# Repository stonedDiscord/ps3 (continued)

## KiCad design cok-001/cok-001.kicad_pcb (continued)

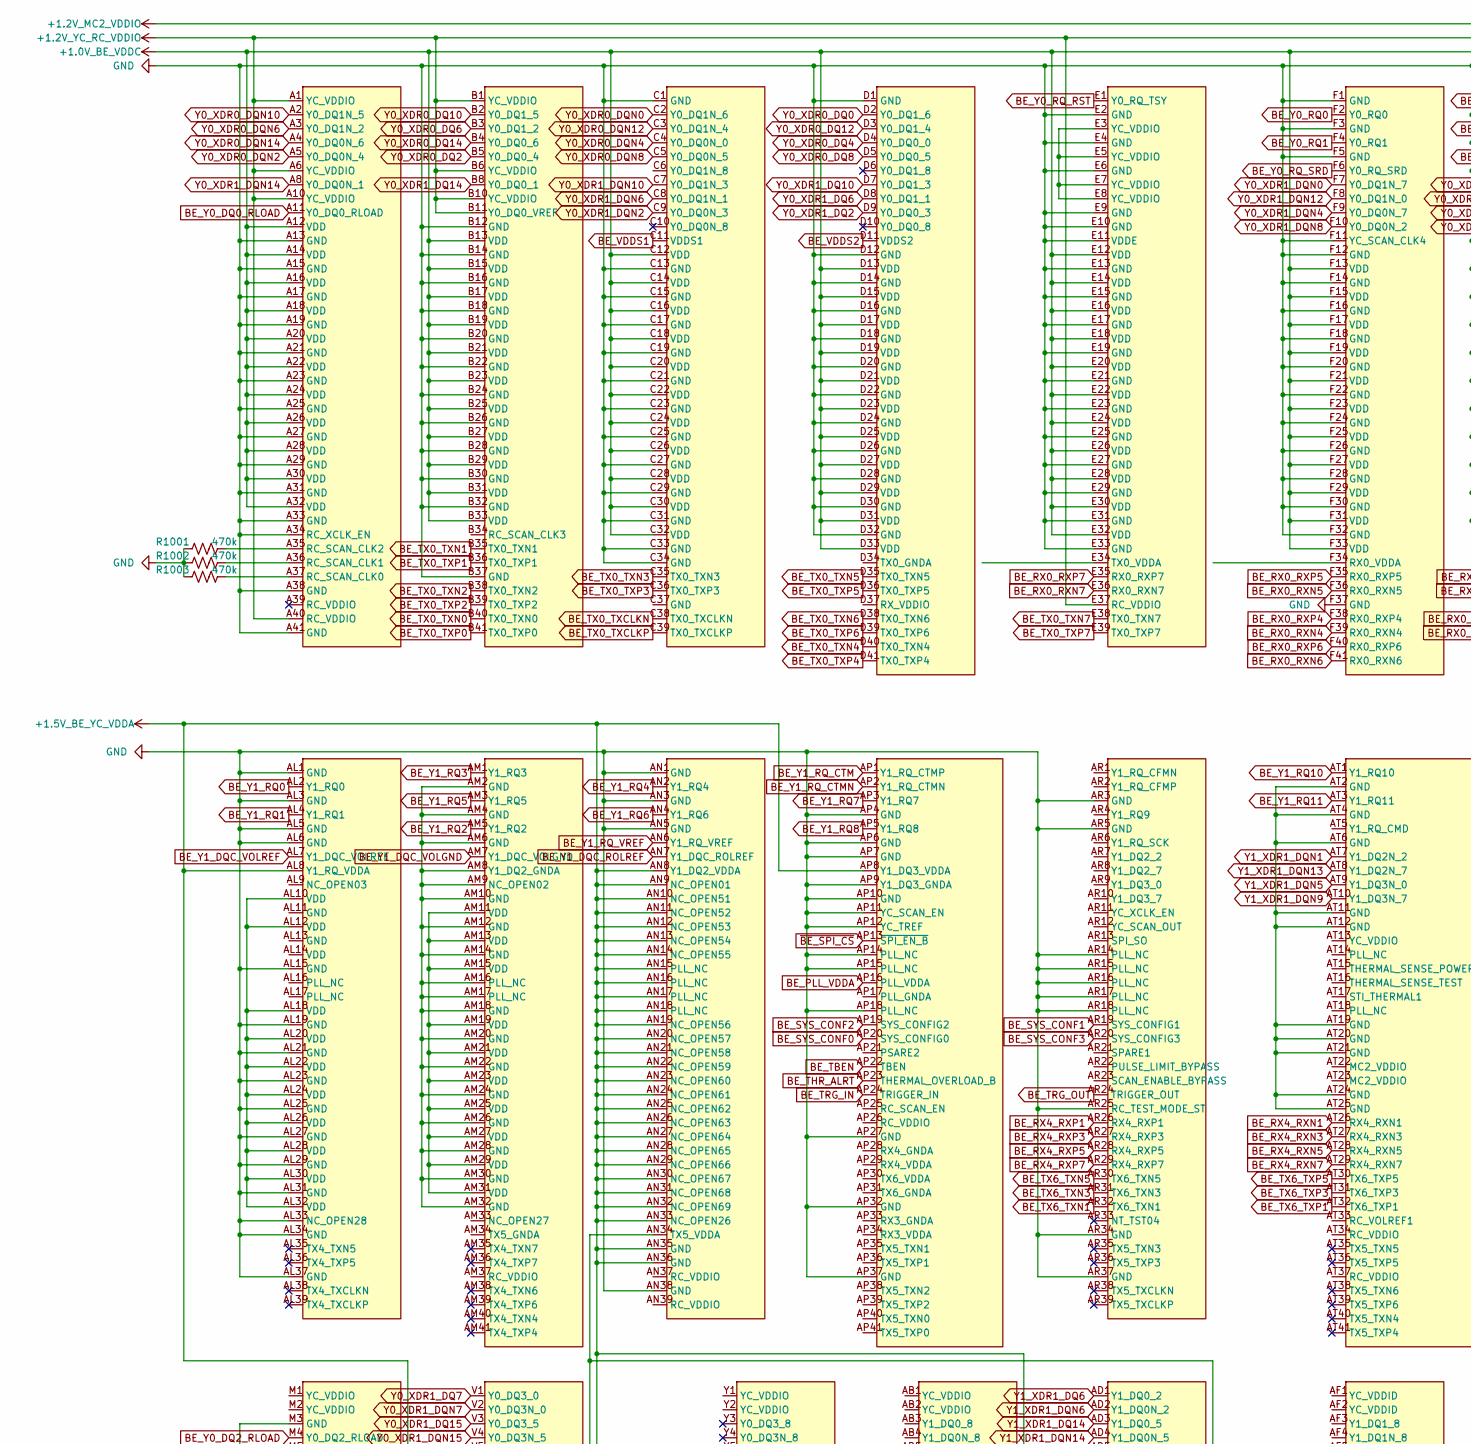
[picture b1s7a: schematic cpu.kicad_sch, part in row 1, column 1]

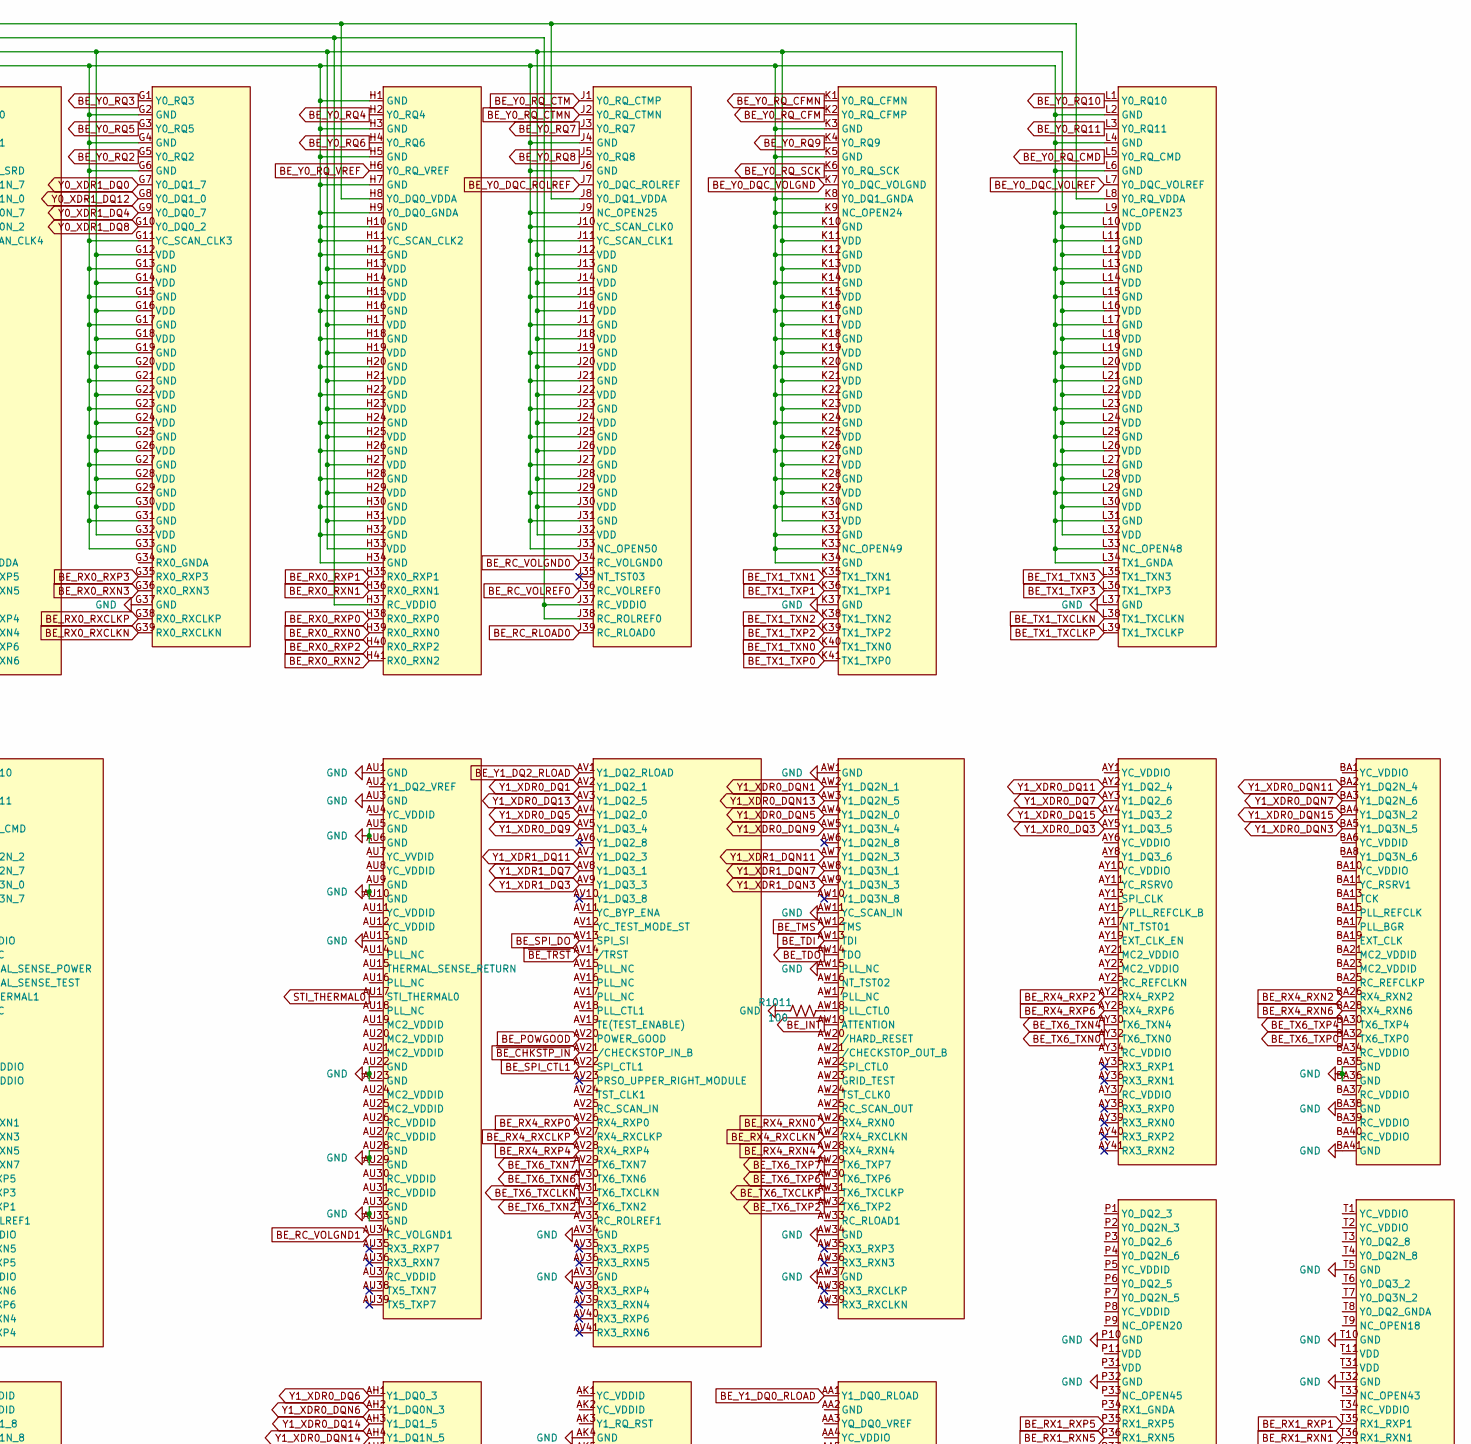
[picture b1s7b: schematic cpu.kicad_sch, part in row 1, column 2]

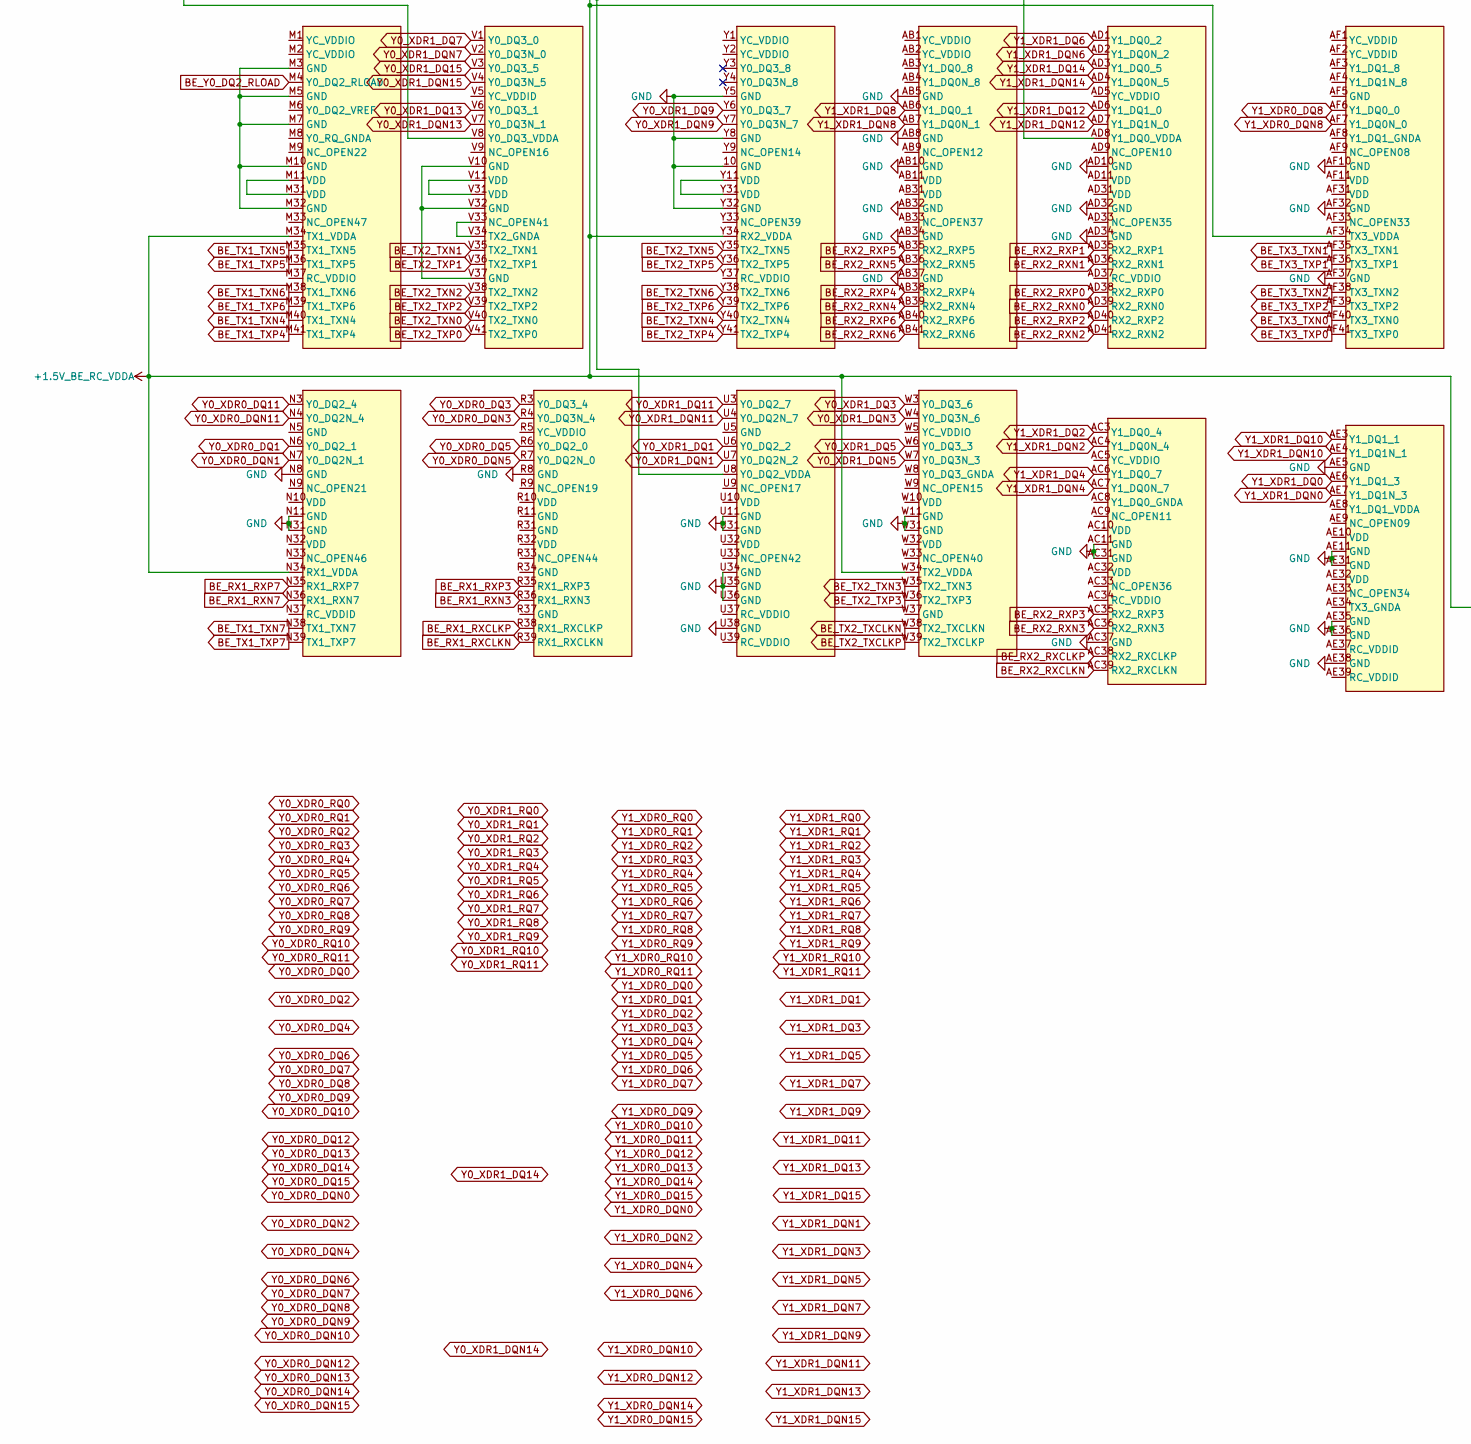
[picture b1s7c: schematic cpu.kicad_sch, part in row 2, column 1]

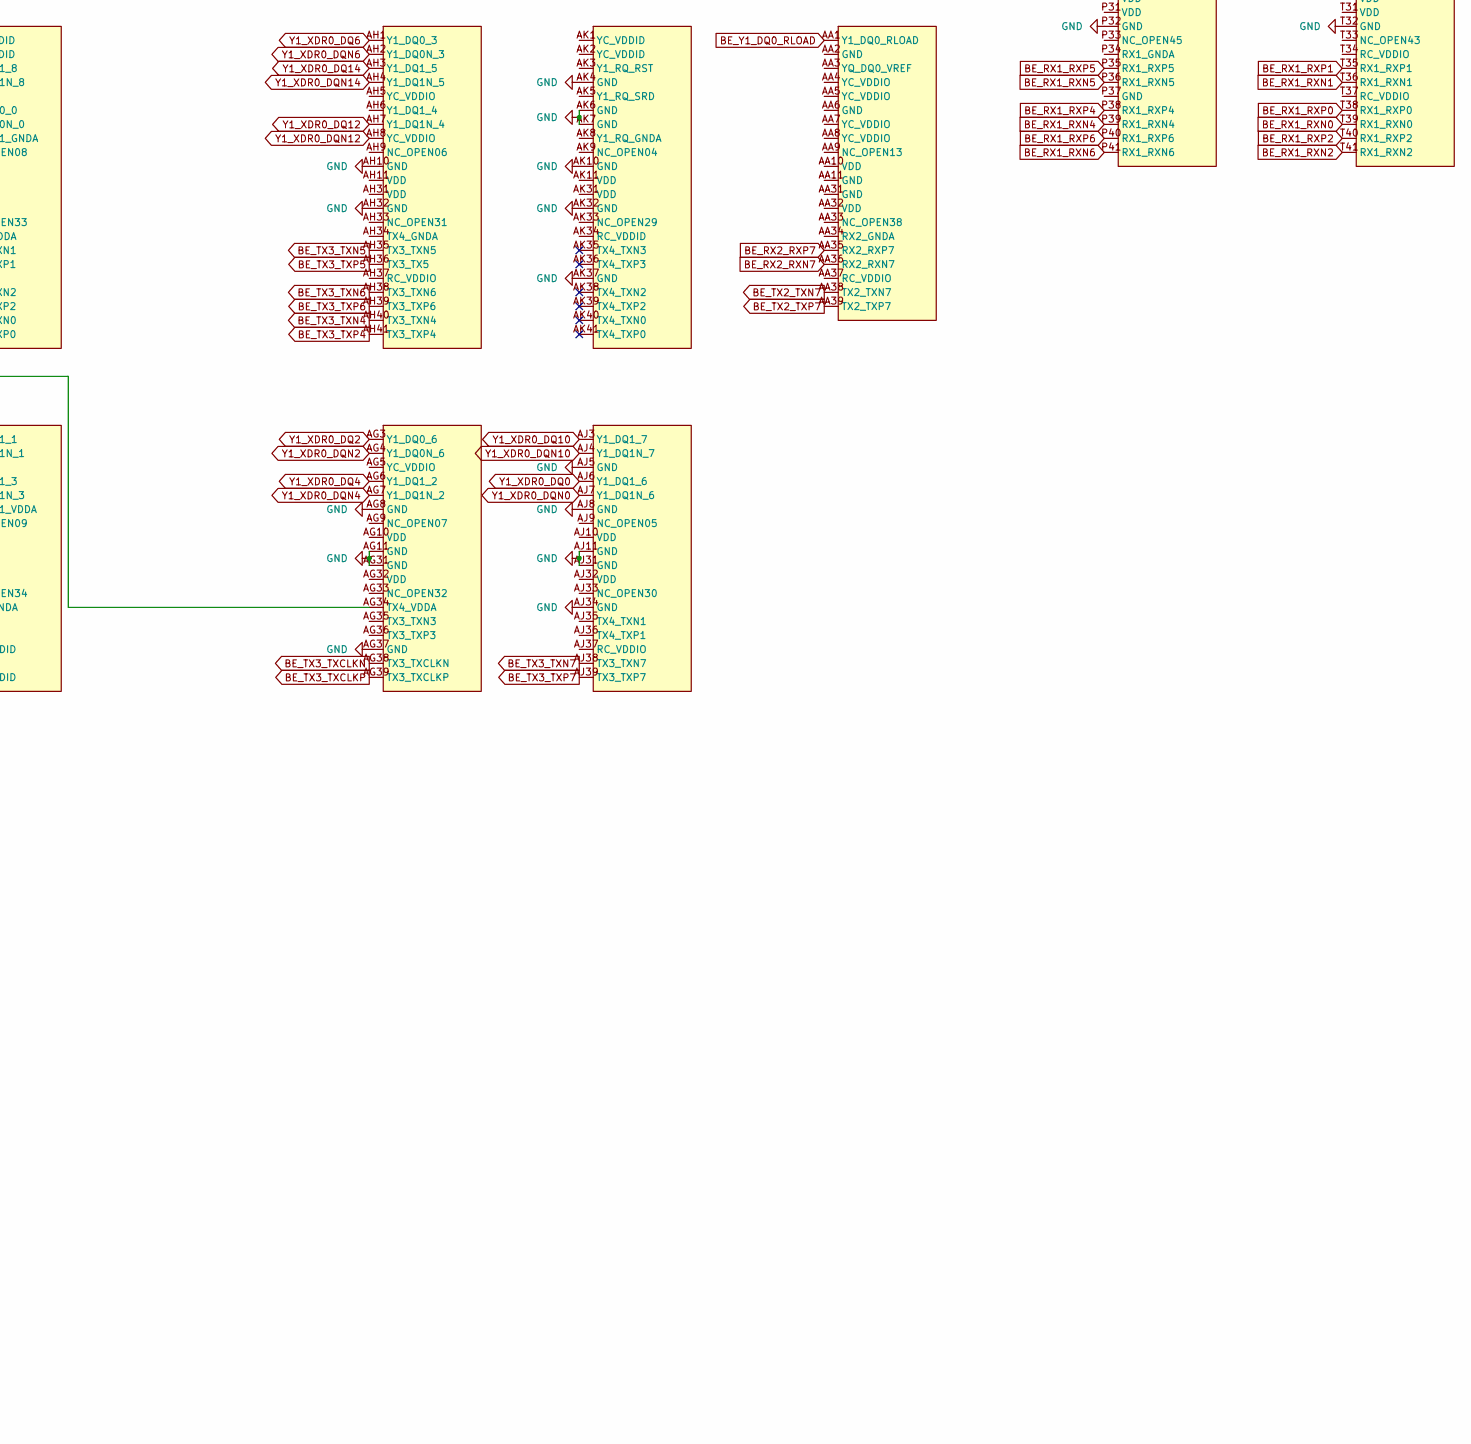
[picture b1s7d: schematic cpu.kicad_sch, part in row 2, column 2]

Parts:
R1001, R1002, R1003: 470k; R_0402_1005Metric
R1011: 100; R_0402_1005Metric
U1001: CELL_multi

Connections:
+1.0V_BE_VDDC: U1001.A12 (VDD), U1001.A14 (VDD), U1001.A16 (VDD), U1001.A18 (VDD), U1001.A20 (VDD), U1001.A22 (VDD), U1001.A24 (VDD), U1001.A26 (VDD), U1001.A28 (VDD), U1001.A30 (VDD), U1001.A32 (VDD), U1001.B13 (VDD), U1001.B15 (VDD), U1001.B17 (VDD), U1001.B19 (VDD), U1001.B21 (VDD), U1001.B23 (VDD), U1001.B25 (VDD), U1001.B27 (VDD), U1001.B29 (VDD), U1001.B31 (VDD), U1001.B33 (VDD), U1001.C12 (VDD), U1001.C14 (VDD), U1001.C16 (VDD), U1001.C18 (VDD), U1001.C20 (VDD), U1001.C22 (VDD), U1001.C24 (VDD), U1001.C26 (VDD), U1001.C28 (VDD), U1001.C30 (VDD), U1001.C32 (VDD), U1001.D13 (VDD), U1001.D15 (VDD), U1001.D17 (VDD), U1001.D19 (VDD), U1001.D21 (VDD), U1001.D23 (VDD), U1001.D25 (VDD), U1001.D27 (VDD), U1001.D29 (VDD), U1001.D31 (VDD), U1001.D33 (VDD), U1001.E12 (VDD), U1001.E14 (VDD), U1001.E16 (VDD), U1001.E18 (VDD), U1001.E20 (VDD), U1001.E22 (VDD), U1001.E24 (VDD), U1001.E26 (VDD), U1001.E28 (VDD), U1001.E30 (VDD), U1001.E32 (VDD), U1001.F13 (VDD), U1001.F15 (VDD), U1001.F17 (VDD), U1001.F19 (VDD), U1001.F21 (VDD), U1001.F23 (VDD), U1001.F25 (VDD), U1001.F27 (VDD), U1001.F29 (VDD), U1001.F31 (VDD), U1001.F33 (VDD), U1001.G12 (VDD), U1001.G14 (VDD), U1001.G16 (VDD), U1001.G18 (VDD), U1001.G20 (VDD), U1001.G22 (VDD), U1001.G24 (VDD), U1001.G26 (VDD), U1001.G28 (VDD), U1001.G30 (VDD), U1001.G32 (VDD), U1001.H13 (VDD), U1001.H15 (VDD), U1001.H17 (VDD), U1001.H19 (VDD), U1001.H21 (VDD), U1001.H23 (VDD), U1001.H25 (VDD), U1001.H27 (VDD), U1001.H29 (VDD), U1001.H31 (VDD), U1001.H33 (VDD), U1001.J12 (VDD), U1001.J14 (VDD), U1001.J16 (VDD), U1001.J18 (VDD), U1001.J20 (VDD), U1001.J22 (VDD), U1001.J24 (VDD), U1001.J26 (VDD), U1001.J28 (VDD), U1001.J30 (VDD), U1001.J32 (VDD), U1001.K11 (VDD), U1001.K13 (VDD), U1001.K15 (VDD), U1001.K17 (VDD), U1001.K19 (VDD), U1001.K21 (VDD), U1001.K23 (VDD), U1001.K25 (VDD), U1001.K27 (VDD), U1001.K29 (VDD), U1001.K31 (VDD), U1001.L10 (VDD), U1001.L12 (VDD), U1001.L14 (VDD), U1001.L16 (VDD), U1001.L18 (VDD), U1001.L20 (VDD), U1001.L22 (VDD), U1001.L24 (VDD), U1001.L26 (VDD), U1001.L28 (VDD), U1001.L30 (VDD), U1001.L32 (VDD); also elsewhere on the board
+1.2V_MC2_VDDIO: U1001.H8 (Y0_DQ0_VDDA), U1001.J8 (Y0_DQ1_VDDA), U1001.L8 (Y0_RQ_VDDA); also elsewhere on the board
+1.2V_YC_RC_VDDIO: U1001.A1 (YC_VDDIO), U1001.A6 (YC_VDDIO), U1001.A10 (YC_VDDIO), U1001.A40 (RC_VDDIO), U1001.B1 (YC_VDDIO), U1001.B6 (YC_VDDIO), U1001.B10 (YC_VDDIO), U1001.B11 (Y0_DQ0_VREF), U1001.E37 (RC_VDDIO), U1001.H37 (RC_VDDIO), U1001.J37 (RC_VDDIO), U1001.J38 (RC_ROLREF0); also elsewhere on the board
+1.5V_BE_RC_VDDA: U1001.AF34 (TX3_VDDA), U1001.AG34 (TX4_VDDA), U1001.AN34 (TX5_VDDA), U1001.M34 (TX1_VDDA), U1001.N34 (RX1_VDDA), U1001.W34 (TX2_VDDA), U1001.Y34 (RX2_VDDA)
+1.5V_BE_YC_VDDA: U1001.AD8 (Y1_DQ0_VDDA), U1001.AL8 (Y1_RQ_VDDA), U1001.AN8 (Y1_DQ2_VDDA), U1001.AN9 (NC_OPEN01), U1001.AN10 (NC_OPEN51), U1001.AN11 (NC_OPEN52), U1001.AN12 (NC_OPEN53), U1001.AN13 (NC_OPEN54), U1001.AN14 (NC_OPEN55), U1001.AN15 (PLL_NC), U1001.AN16 (PLL_NC), U1001.AN17 (PLL_NC), U1001.AN18 (PLL_NC), U1001.AN19 (NC_OPEN56), U1001.AN20 (NC_OPEN57), U1001.AN21 (NC_OPEN58), U1001.AN22 (NC_OPEN59), U1001.AN23 (NC_OPEN60), U1001.AN24 (NC_OPEN61), U1001.AN25 (NC_OPEN62), U1001.AN26 (NC_OPEN63), U1001.AN27 (NC_OPEN64), U1001.AN28 (NC_OPEN65), U1001.AN29 (NC_OPEN66), U1001.AN30 (NC_OPEN67), U1001.AN31 (NC_OPEN68), U1001.AN32 (NC_OPEN69), U1001.AN33 (NC_OPEN26), U1001.AN35 (GND), U1001.AN36 (GND), U1001.AP8 (Y1_DQ3_VDDA), U1001.U8 (Y0_DQ2_VDDA), U1001.V8 (Y0_DQ3_VDDA)
BE_INT: U1001.AW19 (ATTENTION)
BE_PLL_VDDA: U1001.AP16 (PLL_VDDA); also elsewhere on the board
BE_POWGOOD: U1001.AV20 (POWER_GOOD); also elsewhere on the board
BE_RC_RLOAD0: U1001.J39 (RC_RLOAD0); also elsewhere on the board
BE_RC_VOLGND0: U1001.J34 (RC_VOLGND0); also elsewhere on the board
BE_RC_VOLGND1: U1001.AU34 (RC_VOLGND1); also elsewhere on the board
BE_RC_VOLREF0: U1001.J36 (RC_VOLREF0); also elsewhere on the board
BE_RX0_RXCLKN: U1001.G39 (RX0_RXCLKN); also elsewhere on the board
BE_RX0_RXCLKP: U1001.G38 (RX0_RXCLKP); also elsewhere on the board
BE_RX0_RXN0: U1001.H39 (RX0_RXN0); also elsewhere on the board
BE_RX0_RXN1: U1001.H36 (RX0_RXN1); also elsewhere on the board
BE_RX0_RXN2: U1001.H41 (RX0_RXN2); also elsewhere on the board
BE_RX0_RXN3: U1001.G36 (RXO_RXN3); also elsewhere on the board
BE_RX0_RXN4: U1001.F39 (RX0_RXN4); also elsewhere on the board
BE_RX0_RXN5: U1001.F36 (RX0_RXN5); also elsewhere on the board
BE_RX0_RXN6: U1001.F41 (RX0_RXN6); also elsewhere on the board
BE_RX0_RXN7: U1001.E36 (RX0_RXN7); also elsewhere on the board
BE_RX0_RXP0: U1001.H38 (RX0_RXP0); also elsewhere on the board
BE_RX0_RXP1: U1001.H35 (RX0_RXP1); also elsewhere on the board
BE_RX0_RXP2: U1001.H40 (RX0_RXP2); also elsewhere on the board
BE_RX0_RXP3: U1001.G35 (RX0_RXP3); also elsewhere on the board
BE_RX0_RXP4: U1001.F38 (RX0_RXP4); also elsewhere on the board
BE_RX0_RXP5: U1001.F35 (RX0_RXP5); also elsewhere on the board
BE_RX0_RXP6: U1001.F40 (RX0_RXP6); also elsewhere on the board
BE_RX0_RXP7: U1001.E35 (RX0_RXP7); also elsewhere on the board
BE_RX1_RXCLKN: U1001.R39 (RX1_RXCLKN); also elsewhere on the board
BE_RX1_RXCLKP: U1001.R38 (RX1_RXCLKP); also elsewhere on the board
BE_RX1_RXN0: U1001.T39 (RX1_RXN0); also elsewhere on the board
BE_RX1_RXN1: U1001.T36 (RX1_RXN1); also elsewhere on the board
BE_RX1_RXN2: U1001.T41 (RX1_RXN2); also elsewhere on the board
BE_RX1_RXN3: U1001.R36 (RX1_RXN3); also elsewhere on the board
BE_RX1_RXN4: U1001.P39 (RX1_RXN4); also elsewhere on the board
BE_RX1_RXN5: U1001.P36 (RX1_RXN5); also elsewhere on the board
BE_RX1_RXN6: U1001.P41 (RX1_RXN6); also elsewhere on the board
BE_RX1_RXN7: U1001.N36 (RX1_RXN7); also elsewhere on the board
BE_RX1_RXP0: U1001.T38 (RX1_RXP0); also elsewhere on the board
BE_RX1_RXP1: U1001.T35 (RX1_RXP1); also elsewhere on the board
BE_RX1_RXP2: U1001.T40 (RX1_RXP2); also elsewhere on the board
BE_RX1_RXP3: U1001.R35 (RX1_RXP3); also elsewhere on the board
BE_RX1_RXP4: U1001.P38 (RX1_RXP4); also elsewhere on the board
BE_RX1_RXP5: U1001.P35 (RX1_RXP5); also elsewhere on the board
BE_RX1_RXP6: U1001.P40 (RX1_RXP6); also elsewhere on the board
BE_RX1_RXP7: U1001.N35 (RX1_RXP7); also elsewhere on the board
BE_RX2_RXCLKN: U1001.AC39 (RX2_RXCLKN); also elsewhere on the board
BE_RX2_RXCLKP: U1001.AC38 (RX2_RXCLKP); also elsewhere on the board
BE_RX2_RXN0: U1001.AD39 (RX2_RXN0); also elsewhere on the board
BE_RX2_RXN1: U1001.AD36 (RX2_RXN1)
BE_RX2_RXN2: U1001.AD41 (RX2_RXN2); also elsewhere on the board
BE_RX2_RXN3: U1001.AC36 (RX2_RXN3); also elsewhere on the board
BE_RX2_RXN4: U1001.AB39 (RX2_RXN4); also elsewhere on the board
BE_RX2_RXN5: U1001.AB36 (RX2_RXN5); also elsewhere on the board
BE_RX2_RXN6: U1001.AB41 (RX2_RXN6); also elsewhere on the board
BE_RX2_RXN7: U1001.AA36 (RX2_RXN7); also elsewhere on the board
BE_RX2_RXP0: U1001.AD38 (RX2_RXP0); also elsewhere on the board
BE_RX2_RXP1: U1001.AD35 (RX2_RXP1)
BE_RX2_RXP2: U1001.AD40 (RX2_RXP2); also elsewhere on the board
BE_RX2_RXP3: U1001.AC35 (RX2_RXP3); also elsewhere on the board
BE_RX2_RXP4: U1001.AB38 (RX2_RXP4); also elsewhere on the board
BE_RX2_RXP5: U1001.AB35 (RX2_RXP5); also elsewhere on the board
BE_RX2_RXP6: U1001.AB40 (RX2_RXP6); also elsewhere on the board
BE_RX2_RXP7: U1001.AA35 (RX2_RXP7); also elsewhere on the board
BE_RX4_RXCLKN: U1001.AW27 (RX4_RXCLKN); also elsewhere on the board
BE_RX4_RXCLKP: U1001.AV27 (RX4_RXCLKP); also elsewhere on the board
BE_RX4_RXN0: U1001.AW26 (RX4_RXN0); also elsewhere on the board
BE_RX4_RXN1: U1001.AT26 (RX4_RXN1); also elsewhere on the board
BE_RX4_RXN2: U1001.BA26 (RX4_RXN2); also elsewhere on the board
BE_RX4_RXN3: U1001.AT27 (RX4_RXN3); also elsewhere on the board
BE_RX4_RXN4: U1001.AW28 (RX4_RXN4); also elsewhere on the board
BE_RX4_RXN5: U1001.AT28 (RX4_RXN5); also elsewhere on the board
BE_RX4_RXN6: U1001.BA28 (RX4_RXN6); also elsewhere on the board
BE_RX4_RXN7: U1001.AT29 (RX4_RXN7); also elsewhere on the board
BE_RX4_RXP0: U1001.AV26 (RX4_RXP0); also elsewhere on the board
BE_RX4_RXP1: U1001.AR26 (RX4_RXP1); also elsewhere on the board
BE_RX4_RXP2: U1001.AY26 (RX4_RXP2); also elsewhere on the board
BE_RX4_RXP3: U1001.AR27 (RX4_RXP3); also elsewhere on the board
BE_RX4_RXP4: U1001.AV28 (RX4_RXP4); also elsewhere on the board
BE_RX4_RXP5: U1001.AR28 (RX4_RXP5); also elsewhere on the board
BE_RX4_RXP6: U1001.AY28 (RX4_RXP6); also elsewhere on the board
BE_RX4_RXP7: U1001.AR29 (RX4_RXP7); also elsewhere on the board
BE_SPI_CTL1: U1001.AV22 (SPI_CTL1); also elsewhere on the board
BE_SPI_DO: U1001.AV13 (SPI_SI); also elsewhere on the board
BE_SYS_CONF0: U1001.AP20 (SYS_CONFIG0); also elsewhere on the board
BE_SYS_CONF1: U1001.AR19 (SYS_CONFIG1); also elsewhere on the board
BE_SYS_CONF2: U1001.AP19 (SYS_CONFIG2); also elsewhere on the board
BE_SYS_CONF3: U1001.AR20 (SYS_CONFIG3); also elsewhere on the board
BE_TBEN: U1001.AP22 (TBEN); also elsewhere on the board
BE_TDI: U1001.AW13 (TDI); also elsewhere on the board
BE_TDO: U1001.AW14 (TDO); also elsewhere on the board
BE_THR_ALRT: U1001.AP23 (THERMAL_OVERLOAD_B); also elsewhere on the board
BE_TMS: U1001.AW12 (TMS); also elsewhere on the board
BE_TRG_IN: U1001.AP24 (TRIGGER_IN); also elsewhere on the board
BE_TRG_OUT: U1001.AR24 (TRIGGER_OUT); also elsewhere on the board
BE_TX0_TXCLKN: U1001.C38 (TX0_TXCLKN); also elsewhere on the board
BE_TX0_TXCLKP: U1001.C39 (TX0_TXCLKP); also elsewhere on the board
BE_TX0_TXN0: U1001.B40 (TX0_TXN0); also elsewhere on the board
BE_TX0_TXN1: U1001.B35 (TX0_TXN1); also elsewhere on the board
BE_TX0_TXN2: U1001.B38 (TX0_TXN2); also elsewhere on the board
BE_TX0_TXN3: U1001.C35 (TX0_TXN3); also elsewhere on the board
BE_TX0_TXN4: U1001.D40 (TX0_TXN4); also elsewhere on the board
BE_TX0_TXN5: U1001.D35 (TX0_TXN5); also elsewhere on the board
BE_TX0_TXN6: U1001.D38 (TX0_TXN6); also elsewhere on the board
BE_TX0_TXN7: U1001.E38 (TX0_TXN7); also elsewhere on the board
BE_TX0_TXP0: U1001.B41 (TX0_TXP0); also elsewhere on the board
BE_TX0_TXP1: U1001.B36 (TX0_TXP1); also elsewhere on the board
BE_TX0_TXP2: U1001.B39 (TX0_TXP2); also elsewhere on the board
BE_TX0_TXP3: U1001.C36 (TX0_TXP3); also elsewhere on the board
BE_TX0_TXP4: U1001.D41 (TX0_TXP4); also elsewhere on the board
BE_TX0_TXP5: U1001.D36 (TX0_TXP5); also elsewhere on the board
BE_TX0_TXP6: U1001.D39 (TX0_TXP6); also elsewhere on the board
BE_TX0_TXP7: U1001.E39 (TX0_TXP7); also elsewhere on the board
BE_TX1_TXCLKN: U1001.L38 (TX1_TXCLKN); also elsewhere on the board
BE_TX1_TXCLKP: U1001.L39 (TX1_TXCLKP); also elsewhere on the board
BE_TX1_TXN0: U1001.K40 (TX1_TXN0); also elsewhere on the board
BE_TX1_TXN1: U1001.K35 (TX1_TXN1); also elsewhere on the board
BE_TX1_TXN2: U1001.K38 (TX1_TXN2); also elsewhere on the board
BE_TX1_TXN3: U1001.L35 (TX1_TXN3); also elsewhere on the board
BE_TX1_TXN4: U1001.M40 (TX1_TXN4); also elsewhere on the board
BE_TX1_TXN5: U1001.M35 (TX1_TXN5); also elsewhere on the board
BE_TX1_TXN6: U1001.M38 (TX1_TXN6); also elsewhere on the board
BE_TX1_TXN7: U1001.N38 (TX1_TXN7); also elsewhere on the board
BE_TX1_TXP0: U1001.K41 (TX1_TXP0); also elsewhere on the board
BE_TX1_TXP1: U1001.K36 (TX1_TXP1); also elsewhere on the board
BE_TX1_TXP2: U1001.K39 (TX1_TXP2); also elsewhere on the board
BE_TX1_TXP3: U1001.L36 (TX1_TXP3); also elsewhere on the board
BE_TX1_TXP4: U1001.M41 (TX1_TXP4); also elsewhere on the board
BE_TX1_TXP5: U1001.M36 (TX1_TXP5); also elsewhere on the board
BE_TX1_TXP6: U1001.M39 (TX1_TXP6); also elsewhere on the board
BE_TX1_TXP7: U1001.N39 (TX1_TXP7); also elsewhere on the board
BE_TX2_TXCLKN: U1001.W38 (TX2_TXCLKN); also elsewhere on the board
BE_TX2_TXCLKP: U1001.W39 (TX2_TXCLKP); also elsewhere on the board
BE_TX2_TXN0: U1001.V40 (TX2_TXN0); also elsewhere on the board
BE_TX2_TXN1: U1001.V35 (TX2_TXN1); also elsewhere on the board
BE_TX2_TXN2: U1001.V38 (TX2_TXN2); also elsewhere on the board
BE_TX2_TXN3: U1001.W35 (TX2_TXN3); also elsewhere on the board
BE_TX2_TXN4: U1001.Y40 (TX2_TXN4); also elsewhere on the board
BE_TX2_TXN5: U1001.Y35 (TX2_TXN5); also elsewhere on the board
BE_TX2_TXN6: U1001.Y38 (TX2_TXN6); also elsewhere on the board
BE_TX2_TXN7: U1001.AA38 (TX2_TXN7); also elsewhere on the board
BE_TX2_TXP0: U1001.V41 (TX2_TXP0); also elsewhere on the board
BE_TX2_TXP1: U1001.V36 (TX2_TXP1); also elsewhere on the board
BE_TX2_TXP2: U1001.V39 (TX2_TXP2); also elsewhere on the board
BE_TX2_TXP3: U1001.W36 (TX2_TXP3); also elsewhere on the board
BE_TX2_TXP4: U1001.Y41 (TX2_TXP4); also elsewhere on the board
BE_TX2_TXP5: U1001.Y36 (TX2_TXP5); also elsewhere on the board
BE_TX2_TXP6: U1001.Y39 (TX2_TXP6); also elsewhere on the board
BE_TX2_TXP7: U1001.AA39 (TX2_TXP7); also elsewhere on the board
BE_TX3_TXCLKN: U1001.AG38 (TX3_TXCLKN); also elsewhere on the board
BE_TX3_TXCLKP: U1001.AG39 (TX3_TXCLKP); also elsewhere on the board
BE_TX3_TXN0: U1001.AF40 (TX3_TXN0); also elsewhere on the board
BE_TX3_TXN1: U1001.AF35 (TX3_TXN1); also elsewhere on the board
BE_TX3_TXN2: U1001.AF38 (TX3_TXN2); also elsewhere on the board
BE_TX3_TXN4: U1001.AH40 (TX3_TXN4); also elsewhere on the board
BE_TX3_TXN5: U1001.AH35 (TX3_TXN5); also elsewhere on the board
BE_TX3_TXN6: U1001.AH38 (TX3_TXN6); also elsewhere on the board
BE_TX3_TXN7: U1001.AJ38 (TX3_TXN7); also elsewhere on the board
BE_TX3_TXP0: U1001.AF41 (TX3_TXP0); also elsewhere on the board
BE_TX3_TXP1: U1001.AF36 (TX3_TXP1); also elsewhere on the board
BE_TX3_TXP2: U1001.AF39 (TX3_TXP2); also elsewhere on the board
BE_TX3_TXP4: U1001.AH41 (TX3_TXP4); also elsewhere on the board
BE_TX3_TXP5: U1001.AH36 (TX3_TX5); also elsewhere on the board
BE_TX3_TXP6: U1001.AH39 (TX3_TXP6); also elsewhere on the board
BE_TX3_TXP7: U1001.AJ39 (TX3_TXP7); also elsewhere on the board
BE_TX6_TXCLKN: U1001.AV31 (TX6_TXCLKN); also elsewhere on the board
BE_TX6_TXCLKP: U1001.AW31 (TX6_TXCLKP); also elsewhere on the board
BE_TX6_TXN0: U1001.AY32 (TX6_TXN0); also elsewhere on the board
BE_TX6_TXN1: U1001.AR32 (TX6_TXN1); also elsewhere on the board
BE_TX6_TXN2: U1001.AV32 (TX6_TXN2); also elsewhere on the board
BE_TX6_TXN3: U1001.AR31 (TX6_TXN3); also elsewhere on the board
BE_TX6_TXN4: U1001.AY30 (TX6_TXN4); also elsewhere on the board
BE_TX6_TXN5: U1001.AR30 (TX6_TXN5); also elsewhere on the board
BE_TX6_TXN6: U1001.AV30 (TX6_TXN6); also elsewhere on the board
BE_TX6_TXN7: U1001.AV29 (TX6_TXN7); also elsewhere on the board
BE_TX6_TXP0: U1001.BA32 (TX6_TXP0); also elsewhere on the board
BE_TX6_TXP1: U1001.AT32 (TX6_TXP1); also elsewhere on the board
BE_TX6_TXP2: U1001.AW32 (TX6_TXP2); also elsewhere on the board
BE_TX6_TXP3: U1001.AT31 (TX6_TXP3); also elsewhere on the board
BE_TX6_TXP4: U1001.BA30 (TX6_TXP4); also elsewhere on the board
BE_TX6_TXP5: U1001.AT30 (TX6_TXP5); also elsewhere on the board
BE_TX6_TXP6: U1001.AW30 (TX6_TXP6); also elsewhere on the board
BE_TX6_TXP7: U1001.AW29 (TX6_TXP7); also elsewhere on the board
BE_VDDS1: U1001.C11 (VDDS1)
BE_VDDS2: U1001.D11 (VDDS2); also elsewhere on the board
BE_Y0_DQ0_RLOAD: U1001.A11 (Y0_DQ0_RLOAD); also elsewhere on the board
BE_Y0_DQ2_RLOAD: U1001.M4 (Y0_DQ2_RLOAD); also elsewhere on the board
BE_Y0_DQC_ROLREF: U1001.J7 (Y0_DQC_ROLREF); also elsewhere on the board
BE_Y0_DQC_VOLGND: U1001.K7 (Y0_DQC_VOLGND); also elsewhere on the board
BE_Y0_DQC_VOLREF: U1001.L7 (Y0_DQC_VOLREF); also elsewhere on the board
BE_Y0_RQ0: U1001.F2 (Y0_RQ0); also elsewhere on the board
BE_Y0_RQ1: U1001.F4 (Y0_RQ1); also elsewhere on the board
BE_Y0_RQ2: U1001.G5 (Y0_RQ2); also elsewhere on the board
BE_Y0_RQ3: U1001.G1 (Y0_RQ3); also elsewhere on the board
BE_Y0_RQ4: U1001.H2 (Y0_RQ4); also elsewhere on the board
BE_Y0_RQ5: U1001.G3 (Y0_RQ5); also elsewhere on the board
BE_Y0_RQ6: U1001.H4 (Y0_RQ6); also elsewhere on the board
BE_Y0_RQ7: U1001.J3 (Y0_RQ7); also elsewhere on the board
BE_Y0_RQ8: U1001.J5 (Y0_RQ8); also elsewhere on the board
BE_Y0_RQ9: U1001.K4 (Y0_RQ9); also elsewhere on the board
BE_Y0_RQ10: U1001.L1 (Y0_RQ10); also elsewhere on the board
BE_Y0_RQ11: U1001.L3 (Y0_RQ11); also elsewhere on the board
BE_Y0_RQ_CFM: U1001.K2 (Y0_RQ_CFMP); also elsewhere on the board
BE_Y0_RQ_CFMN: U1001.K1 (Y0_RQ_CFMN); also elsewhere on the board
BE_Y0_RQ_CMD: U1001.L5 (Y0_RQ_CMD)
BE_Y0_RQ_CTM: U1001.J1 (Y0_RQ_CTMP)
BE_Y0_RQ_CTMN: U1001.J2 (Y0_RQ_CTMN)
BE_Y0_RQ_RST: U1001.E1 (Y0_RQ_TSY)
BE_Y0_RQ_SCK: U1001.K6 (Y0_RQ_SCK); also elsewhere on the board
BE_Y0_RQ_SRD: U1001.F6 (Y0_RQ_SRD)
BE_Y0_RQ_VREF: U1001.H6 (Y0_RQ_VREF)
BE_Y1_DQ0_RLOAD: U1001.AA1 (Y1_DQ0_RLOAD); also elsewhere on the board
BE_Y1_DQ2_RLOAD: U1001.AV1 (Y1_DQ2_RLOAD); also elsewhere on the board
BE_Y1_DQC_ROLREF: U1001.AN7 (Y1_DQC_ROLREF); also elsewhere on the board
BE_Y1_DQC_VOLGND: U1001.AM7 (Y1_DQC_VOLGND); also elsewhere on the board
BE_Y1_DQC_VOLREF: U1001.AL7 (Y1_DQC_VOLREF); also elsewhere on the board
BE_Y1_RQ0: U1001.AL2 (Y1_RQ0); also elsewhere on the board
BE_Y1_RQ1: U1001.AL4 (Y1_RQ1); also elsewhere on the board
BE_Y1_RQ2: U1001.AM5 (Y1_RQ2); also elsewhere on the board
BE_Y1_RQ3: U1001.AM1 (Y1_RQ3); also elsewhere on the board
BE_Y1_RQ4: U1001.AN2 (Y1_RQ4); also elsewhere on the board
BE_Y1_RQ5: U1001.AM3 (Y1_RQ5); also elsewhere on the board
BE_Y1_RQ6: U1001.AN4 (Y1_RQ6); also elsewhere on the board
BE_Y1_RQ7: U1001.AP3 (Y1_RQ7); also elsewhere on the board
BE_Y1_RQ8: U1001.AP5 (Y1_RQ8); also elsewhere on the board
BE_Y1_RQ10: U1001.AT1 (Y1_RQ10); also elsewhere on the board
BE_Y1_RQ11: U1001.AT3 (Y1_RQ11); also elsewhere on the board
BE_Y1_RQ_CTM: U1001.AP1 (Y1_RQ_CTMP)
BE_Y1_RQ_CTMN: U1001.AP2 (Y1_RQ_CTMN)
BE_Y1_RQ_VREF: U1001.AN6 (Y1_RQ_VREF)
GND: R1001.1, R1002.1, R1003.1, R1011.1, U1001.10 (GND), U1001.A13 (GND), U1001.A15 (GND), U1001.A17 (GND), U1001.A19 (GND), U1001.A21 (GND), U1001.A23 (GND), U1001.A25 (GND), U1001.A27 (GND), U1001.A29 (GND), U1001.A31 (GND), U1001.A33 (GND), U1001.A34 (RC_XCLK_EN), U1001.A38 (GND), U1001.A41 (GND), U1001.AB5 (GND), U1001.AB8 (GND), U1001.AB10 (GND), U1001.AB32 (GND), U1001.AB34 (GND), U1001.AB37 (GND), U1001.AC11 (GND), U1001.AC31 (GND), U1001.AC37 (GND), U1001.AD10 (GND), U1001.AD32 (GND), U1001.AD34 (GND), U1001.AE5 (GND), U1001.AE11 (GND), U1001.AE31 (GND), U1001.AE35 (GND), U1001.AE36 (GND), U1001.AE38 (GND), U1001.AF10 (GND), U1001.AF32 (GND), U1001.AF37 (GND), U1001.AG8 (GND), U1001.AG11 (GND), U1001.AG31 (GND), U1001.AG37 (GND), U1001.AH10 (GND), U1001.AH32 (GND), U1001.AJ5 (GND), U1001.AJ8 (GND), U1001.AJ11 (GND), U1001.AJ31 (GND), U1001.AJ34 (GND), U1001.AK4 (GND), U1001.AK6 (GND), U1001.AK7 (GND), U1001.AK10 (GND), U1001.AK32 (GND), U1001.AK37 (GND), U1001.AL1 (GND), U1001.AL3 (GND), U1001.AL5 (GND), U1001.AL6 (GND), U1001.AL15 (GND), U1001.AL19 (GND), U1001.AL21 (GND), U1001.AL23 (GND), U1001.AL25 (GND), U1001.AL27 (GND), U1001.AL29 (GND), U1001.AL31 (GND), U1001.AL33 (NC_OPEN28), U1001.AL34 (GND), U1001.AL37 (GND), U1001.AN1 (GND), U1001.AN3 (GND), U1001.AN5 (GND), U1001.AN38 (GND), U1001.AP4 (GND), U1001.AP6 (GND), U1001.AP7 (GND), U1001.AP9 (Y1_DQ3_GNDA), U1001.AP10 (GND), U1001.AP11 (YC_SCAN_EN), U1001.AP12 (YC_TREF), U1001.AP14 (PLL_NC), U1001.AP15 (PLL_NC), U1001.AP18 (PLL_NC), U1001.AP27 (GND), U1001.AP32 (GND), U1001.AP37 (GND), U1001.AR3 (GND), U1001.AR5 (GND), U1001.AR14 (PLL_NC), U1001.AR15 (PLL_NC), U1001.AR16 (PLL_NC), U1001.AR17 (PLL_NC), U1001.AR18 (PLL_NC), U1001.AR25 (RC_TEST_MODE_ST), U1001.AR34 (GND), U1001.AR37 (GND), U1001.AU1 (GND), U1001.AU3 (GND), U1001.AU5 (GND), U1001.AU6 (GND), U1001.AU9 (GND), U1001.AU10 (GND), U1001.AU13 (GND), U1001.AU22 (GND), U1001.AU23 (GND), U1001.AU28 (GND), U1001.AU29 (GND), U1001.AU32 (GND), U1001.AU33 (GND), U1001.AV34 (GND), U1001.AV37 (GND), U1001.AW1 (GND), U1001.AW11 (YC_SCAN_IN), U1001.AW15 (PLL_NC), U1001.AW34 (GND), U1001.AW37 (GND), U1001.B12 (GND), U1001.B14 (GND), U1001.B16 (GND), U1001.B18 (GND), U1001.B20 (GND), U1001.B22 (GND), U1001.B24 (GND), U1001.B26 (GND), U1001.B28 (GND), U1001.B30 (GND), U1001.B32 (GND), U1001.B37 (GND), U1001.BA35 (GND), U1001.BA36 (GND), U1001.BA38 (GND), U1001.BA41 (GND), U1001.C1 (GND), U1001.C13 (GND), U1001.C15 (GND), U1001.C17 (GND), U1001.C19 (GND), U1001.C21 (GND), U1001.C23 (GND), U1001.C25 (GND), U1001.C27 (GND), U1001.C29 (GND), U1001.C31 (GND), U1001.C33 (GND), U1001.C34 (GND), U1001.D1 (GND), U1001.D12 (GND), U1001.D14 (GND), U1001.D16 (GND), U1001.D18 (GND), U1001.D20 (GND), U1001.D22 (GND), U1001.D24 (GND), U1001.D26 (GND), U1001.D28 (GND), U1001.D30 (GND), U1001.D32 (GND), U1001.E2 (GND), U1001.E4 (GND), U1001.E6 (GND), U1001.E9 (GND), U1001.E10 (GND), U1001.E11 (VDDE), U1001.E13 (GND), U1001.E15 (GND), U1001.E17 (GND), U1001.E19 (GND), U1001.E21 (GND), U1001.E23 (GND), U1001.E25 (GND), U1001.E27 (GND), U1001.E29 (GND), U1001.E31 (GND), U1001.E33 (GND), U1001.F1 (GND), U1001.F3 (GND), U1001.F5 (GND), U1001.F11 (YC_SCAN_CLK4), U1001.F12 (GND), U1001.F14 (GND), U1001.F16 (GND), U1001.F18 (GND), U1001.F20 (GND), U1001.F22 (GND), U1001.F24 (GND), U1001.F26 (GND), U1001.F28 (GND), U1001.F30 (GND), U1001.F32 (GND), U1001.F37 (GND), U1001.G2 (GND), U1001.G4 (GND), U1001.G6 (GND), U1001.G11 (YC_SCAN_CLK3), U1001.G13 (GND), U1001.G15 (GND), U1001.G17 (GND), U1001.G19 (GND), U1001.G21 (GND), U1001.G23 (GND), U1001.G25 (GND), U1001.G27 (GND), U1001.G29 (GND), U1001.G31 (GND), U1001.G33 (GND), U1001.G37 (GND)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; also elsewhere on the board
unnamed: R1003.2, U1001.A37 (RC_SCAN_CLK0)
unnamed: R1002.2, U1001.A36 (RC_SCAN_CLK1)
unnamed: R1001.2, U1001.A35 (RC_SCAN_CLK2)
unnamed: U1001.AL10 (VDD), U1001.AL12 (VDD), U1001.AL18 (VDD), U1001.AL20 (VDD), U1001.AL22 (VDD), U1001.AL24 (VDD), U1001.AL26 (VDD), U1001.AL28 (VDD), U1001.AL30 (VDD), U1001.AL32 (VDD)
unnamed: U1001.AM2 (GND), U1001.AM4 (GND), U1001.AM6 (GND), U1001.AM8 (Y1_DQ2_GNDA), U1001.AM9 (NC_OPEN02), U1001.AM10 (GND), U1001.AM12 (GND), U1001.AM14 (GND), U1001.AM16 (PLL_NC), U1001.AM17 (PLL_NC), U1001.AM18 (GND), U1001.AM20 (GND), U1001.AM22 (GND), U1001.AM24 (GND), U1001.AM26 (GND), U1001.AM28 (GND), U1001.AM30 (GND), U1001.AM32 (GND)
unnamed: U1001.AM11 (VDD), U1001.AM13 (VDD), U1001.AM15 (VDD), U1001.AM19 (VDD), U1001.AM21 (VDD), U1001.AM23 (VDD), U1001.AM25 (VDD), U1001.AM27 (VDD), U1001.AM29 (VDD), U1001.AM31 (VDD)
unnamed: U1001.AT2 (GND), U1001.AT4 (GND), U1001.AT6 (GND), U1001.AT11 (GND), U1001.AT12 (GND), U1001.AT19 (GND), U1001.AT20 (GND), U1001.AT21 (GND), U1001.AT24 (GND), U1001.AT25 (GND)
unnamed: R1011.2, U1001.AW18 (PLL_CTL0)
unnamed: U1001.E3 (YC_VDDIO), U1001.E5 (YC_VDDIO), U1001.E7 (YC_VDDIO), U1001.E8 (YC_VDDIO)
unnamed: U1001.M3 (GND), U1001.M5 (GND), U1001.M7 (GND), U1001.M10 (GND), U1001.M32 (GND)
unnamed: U1001.M11 (VDD), U1001.M31 (VDD)
unnamed: U1001.V10 (GND), U1001.V32 (GND), U1001.V37 (GND)
unnamed: U1001.V33 (NC_OPEN41), U1001.V34 (TX2_GNDA)
unnamed: U1001.V11 (VDD), U1001.V31 (VDD)
unnamed: U1001.Y11 (VDD), U1001.Y31 (VDD)
STI_THERMAL0: U1001.AU17 (STI_THERMAL0); also elsewhere on the board
Y0_XDR0_DQ0: U1001.D2 (Y0_DQ1_6); also elsewhere on the board
Y0_XDR0_DQ1: U1001.N6 (Y0_DQ2_1); also elsewhere on the board
Y0_XDR0_DQ2: U1001.B5 (Y0_DQ0_4); also elsewhere on the board
Y0_XDR0_DQ3: U1001.R3 (Y0_DQ3_4); also elsewhere on the board
Y0_XDR0_DQ4: U1001.D4 (Y0_DQ0_0); also elsewhere on the board
Y0_XDR0_DQ5: U1001.R6 (Y0_DQ2_0); also elsewhere on the board
Y0_XDR0_DQ6: U1001.B3 (Y0_DQ1_2); also elsewhere on the board
Y0_XDR0_DQ8: U1001.D5 (Y0_DQ0_5); also elsewhere on the board
Y0_XDR0_DQ10: U1001.B2 (Y0_DQ1_5); also elsewhere on the board
Y0_XDR0_DQ11: U1001.N3 (Y0_DQ2_4); also elsewhere on the board
Y0_XDR0_DQ12: U1001.D3 (Y0_DQ1_4); also elsewhere on the board
Y0_XDR0_DQ14: U1001.B4 (Y0_DQ0_6); also elsewhere on the board
Y0_XDR0_DQN0: U1001.C2 (Y0_DQ1N_6); also elsewhere on the board
Y0_XDR0_DQN1: U1001.N7 (Y0_DQ2N_1); also elsewhere on the board
Y0_XDR0_DQN2: U1001.A5 (Y0_DQ0N_4); also elsewhere on the board
Y0_XDR0_DQN3: U1001.R4 (Y0_DQ3N_4); also elsewhere on the board
Y0_XDR0_DQN4: U1001.C4 (Y0_DQ0N_0); also elsewhere on the board
Y0_XDR0_DQN5: U1001.R7 (Y0_DQ2N_0); also elsewhere on the board
Y0_XDR0_DQN6: U1001.A3 (Y0_DQ1N_2); also elsewhere on the board
Y0_XDR0_DQN8: U1001.C5 (Y0_DQ0N_5); also elsewhere on the board
Y0_XDR0_DQN10: U1001.A2 (Y0_DQ1N_5); also elsewhere on the board
Y0_XDR0_DQN11: U1001.N4 (Y0_DQ2N_4); also elsewhere on the board
Y0_XDR0_DQN12: U1001.C3 (Y0_DQ1N_4); also elsewhere on the board
Y0_XDR0_DQN14: U1001.A4 (Y0_DQ0N_6); also elsewhere on the board
Y0_XDR1_DQ0: U1001.G7 (Y0_DQ1_7); also elsewhere on the board
Y0_XDR1_DQ1: U1001.U6 (Y0_DQ2_2); also elsewhere on the board
Y0_XDR1_DQ2: U1001.D9 (Y0_DQ0_3); also elsewhere on the board
Y0_XDR1_DQ3: U1001.W3 (Y0_DQ3_6); also elsewhere on the board
Y0_XDR1_DQ4: U1001.G9 (Y0_DQ0_7); also elsewhere on the board
Y0_XDR1_DQ5: U1001.W6 (Y0_DQ3_3); also elsewhere on the board
Y0_XDR1_DQ6: U1001.D8 (Y0_DQ1_1); also elsewhere on the board
Y0_XDR1_DQ7: U1001.V1 (Y0_DQ3_0); also elsewhere on the board
Y0_XDR1_DQ8: U1001.G10 (Y0_DQ0_2); also elsewhere on the board
Y0_XDR1_DQ9: U1001.Y6 (Y0_DQ3_7); also elsewhere on the board
Y0_XDR1_DQ10: U1001.D7 (Y0_DQ1_3); also elsewhere on the board
Y0_XDR1_DQ11: U1001.U3 (Y0_DQ2_7); also elsewhere on the board
Y0_XDR1_DQ12: U1001.G8 (Y0_DQ1_0); also elsewhere on the board
Y0_XDR1_DQ13: U1001.V6 (Y0_DQ3_1); also elsewhere on the board
Y0_XDR1_DQ14: U1001.B8 (Y0_DQ0_1); also elsewhere on the board
Y0_XDR1_DQ15: U1001.V3 (Y0_DQ3_5); also elsewhere on the board
Y0_XDR1_DQN0: U1001.F7 (Y0_DQ1N_7); also elsewhere on the board
Y0_XDR1_DQN1: U1001.U7 (Y0_DQ2N_2); also elsewhere on the board
Y0_XDR1_DQN2: U1001.C9 (Y0_DQ0N_3); also elsewhere on the board
Y0_XDR1_DQN3: U1001.W4 (Y0_DQ3N_6); also elsewhere on the board
Y0_XDR1_DQN4: U1001.F9 (Y0_DQ0N_7); also elsewhere on the board
Y0_XDR1_DQN5: U1001.W7 (Y0_DQ3N_3); also elsewhere on the board
Y0_XDR1_DQN6: U1001.C8 (Y0_DQ1N_1); also elsewhere on the board
Y0_XDR1_DQN7: U1001.V2 (Y0_DQ3N_0); also elsewhere on the board
Y0_XDR1_DQN8: U1001.F10 (Y0_DQ0N_2); also elsewhere on the board
Y0_XDR1_DQN9: U1001.Y7 (Y0_DQ3N_7); also elsewhere on the board
Y0_XDR1_DQN10: U1001.C7 (Y0_DQ1N_3); also elsewhere on the board
Y0_XDR1_DQN11: U1001.U4 (Y0_DQ2N_7); also elsewhere on the board
Y0_XDR1_DQN12: U1001.F8 (Y0_DQ1N_0); also elsewhere on the board
Y0_XDR1_DQN13: U1001.V7 (Y0_DQ3N_1); also elsewhere on the board
Y0_XDR1_DQN14: U1001.A8 (Y0_DQ0N_1); also elsewhere on the board
Y0_XDR1_DQN15: U1001.V4 (Y0_DQ3N_5); also elsewhere on the board
Y1_XDR0_DQ0: U1001.AJ6 (Y1_DQ1_6); also elsewhere on the board
Y1_XDR0_DQ1: U1001.AV2 (Y1_DQ2_1); also elsewhere on the board
Y1_XDR0_DQ2: U1001.AG3 (Y1_DQ0_6); also elsewhere on the board
Y1_XDR0_DQ3: U1001.AY5 (Y1_DQ3_5); also elsewhere on the board
Y1_XDR0_DQ4: U1001.AG6 (Y1_DQ1_2); also elsewhere on the board
Y1_XDR0_DQ5: U1001.AV4 (Y1_DQ2_0); also elsewhere on the board
Y1_XDR0_DQ6: U1001.AH1 (Y1_DQ0_3); also elsewhere on the board
Y1_XDR0_DQ7: U1001.AY3 (Y1_DQ2_6); also elsewhere on the board
Y1_XDR0_DQ8: U1001.AF6 (Y1_DQ0_0); also elsewhere on the board
Y1_XDR0_DQ9: U1001.AV5 (Y1_DQ3_4); also elsewhere on the board
Y1_XDR0_DQ10: U1001.AJ3 (Y1_DQ1_7); also elsewhere on the board
Y1_XDR0_DQ11: U1001.AY2 (Y1_DQ2_4); also elsewhere on the board
Y1_XDR0_DQ12: U1001.AH7 (Y1_DQ1N_4); also elsewhere on the board
Y1_XDR0_DQ13: U1001.AV3 (Y1_DQ2_5); also elsewhere on the board
Y1_XDR0_DQ14: U1001.AH3 (Y1_DQ1_5); also elsewhere on the board
Y1_XDR0_DQ15: U1001.AY4 (Y1_DQ3_2); also elsewhere on the board
Y1_XDR0_DQN0: U1001.AJ7 (Y1_DQ1N_6); also elsewhere on the board
Y1_XDR0_DQN1: U1001.AW2 (Y1_DQ2N_1); also elsewhere on the board
Y1_XDR0_DQN2: U1001.AG4 (Y1_DQ0N_6); also elsewhere on the board
Y1_XDR0_DQN3: U1001.BA5 (Y1_DQ3N_5); also elsewhere on the board
Y1_XDR0_DQN4: U1001.AG7 (Y1_DQ1N_2); also elsewhere on the board
Y1_XDR0_DQN5: U1001.AW4 (Y1_DQ2N_0); also elsewhere on the board
Y1_XDR0_DQN6: U1001.AH2 (Y1_DQ0N_3); also elsewhere on the board
Y1_XDR0_DQN7: U1001.BA3 (Y1_DQ2N_6); also elsewhere on the board
Y1_XDR0_DQN8: U1001.AF7 (Y1_DQ0N_0); also elsewhere on the board
Y1_XDR0_DQN9: U1001.AW5 (Y1_DQ3N_4); also elsewhere on the board
Y1_XDR0_DQN10: U1001.AJ4 (Y1_DQ1N_7); also elsewhere on the board
Y1_XDR0_DQN11: U1001.BA2 (Y1_DQ2N_4); also elsewhere on the board
Y1_XDR0_DQN12: U1001.AH8 (YC_VDDIO); also elsewhere on the board
Y1_XDR0_DQN13: U1001.AW3 (Y1_DQ2N_5); also elsewhere on the board
Y1_XDR0_DQN14: U1001.AH4 (Y1_DQ1N_5); also elsewhere on the board
Y1_XDR0_DQN15: U1001.BA4 (Y1_DQ3N_2); also elsewhere on the board
Y1_XDR1_DQ0: U1001.AE6 (Y1_DQ1_3); also elsewhere on the board
Y1_XDR1_DQ2: U1001.AC3 (Y1_DQ0_4); also elsewhere on the board
Y1_XDR1_DQ3: U1001.AV9 (Y1_DQ3_3); also elsewhere on the board
Y1_XDR1_DQ4: U1001.AC6 (Y1_DQ0_7); also elsewhere on the board
Y1_XDR1_DQ6: U1001.AD1 (Y1_DQ0_2); also elsewhere on the board
Y1_XDR1_DQ7: U1001.AV8 (Y1_DQ3_1); also elsewhere on the board
Y1_XDR1_DQ8: U1001.AB6 (Y1_DQ0_1); also elsewhere on the board
Y1_XDR1_DQ10: U1001.AE3 (Y1_DQ1_1); also elsewhere on the board
Y1_XDR1_DQ11: U1001.AV7 (Y1_DQ2_3); also elsewhere on the board
Y1_XDR1_DQ12: U1001.AD6 (Y1_DQ1_0); also elsewhere on the board
Y1_XDR1_DQ14: U1001.AD3 (Y1_DQ0_5); also elsewhere on the board
Y1_XDR1_DQN0: U1001.AE7 (Y1_DQ1N_3); also elsewhere on the board
Y1_XDR1_DQN1: U1001.AT7 (Y1_DQ2N_2); also elsewhere on the board
Y1_XDR1_DQN2: U1001.AC4 (Y1_DQ0N_4); also elsewhere on the board
Y1_XDR1_DQN3: U1001.AW9 (Y1_DQ3N_3); also elsewhere on the board
Y1_XDR1_DQN4: U1001.AC7 (Y1_DQ0N_7); also elsewhere on the board
Y1_XDR1_DQN5: U1001.AT9 (Y1_DQ3N_0); also elsewhere on the board
Y1_XDR1_DQN6: U1001.AD2 (Y1_DQ0N_2); also elsewhere on the board
Y1_XDR1_DQN7: U1001.AW8 (Y1_DQ3N_1); also elsewhere on the board
Y1_XDR1_DQN8: U1001.AB7 (Y1_DQ0N_1); also elsewhere on the board
Y1_XDR1_DQN9: U1001.AT10 (Y1_DQ3N_7); also elsewhere on the board
Y1_XDR1_DQN10: U1001.AE4 (Y1_DQ1N_1); also elsewhere on the board
Y1_XDR1_DQN11: U1001.AW7 (Y1_DQ2N_3); also elsewhere on the board
Y1_XDR1_DQN12: U1001.AD7 (Y1_DQ1N_0); also elsewhere on the board
Y1_XDR1_DQN13: U1001.AT8 (Y1_DQ2N_7); also elsewhere on the board
Y1_XDR1_DQN14: U1001.AD4 (Y1_DQ0N_5); also elsewhere on the board
~BE_CHKSTP_IN: U1001.AV21 (/CHECKSTOP_IN_B); also elsewhere on the board
~BE_SPI_CS: U1001.AP13 (~SPI_EN_B); also elsewhere on the board
~BE_TRST: U1001.AV14 (/TRST); also elsewhere on the board
